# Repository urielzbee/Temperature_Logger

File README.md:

# Temperature_Logger
Temperature Data Logger

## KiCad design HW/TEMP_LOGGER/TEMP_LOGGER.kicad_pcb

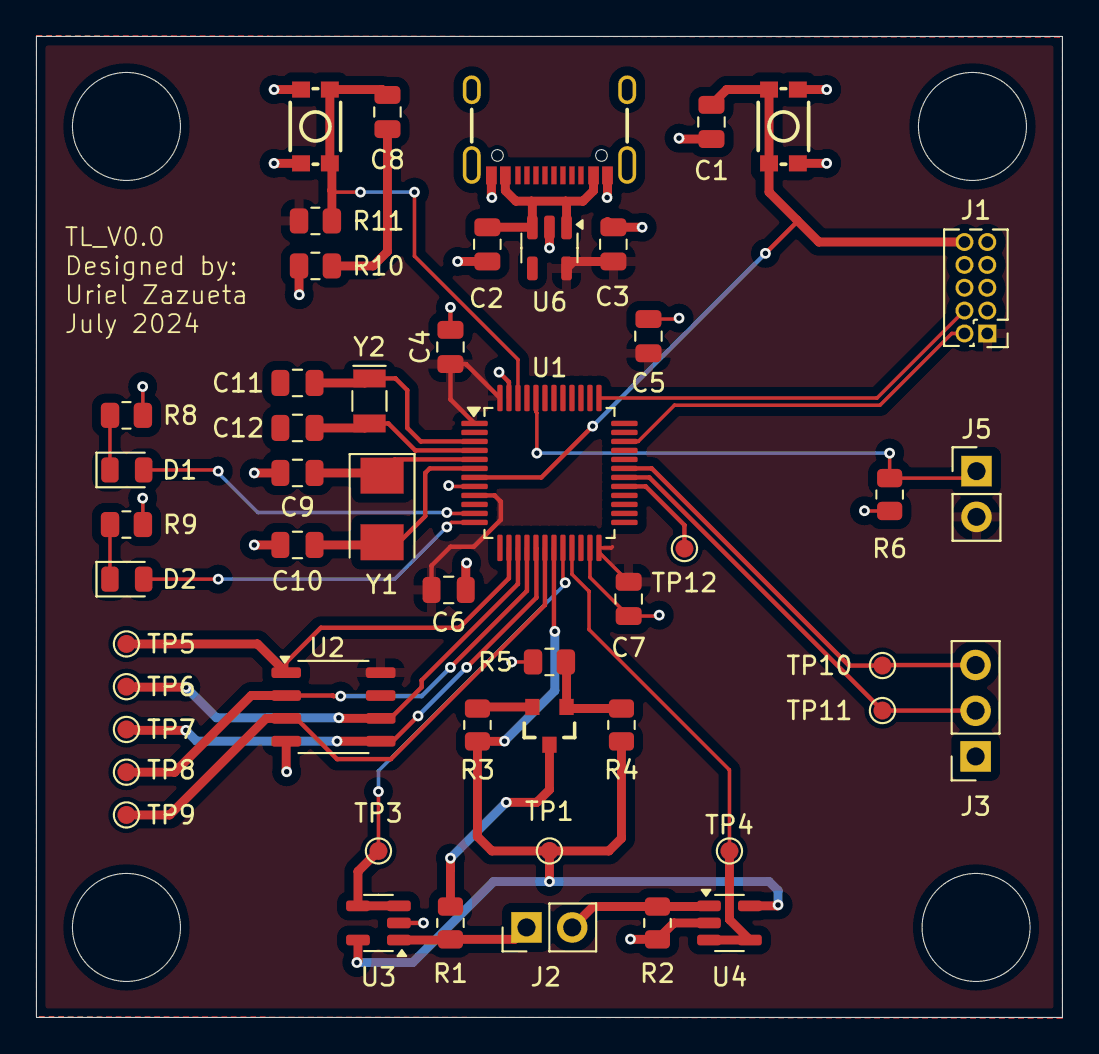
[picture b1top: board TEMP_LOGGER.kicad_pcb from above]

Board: 2 copper layers, 57.0 x 54.5 mm, 50 parts (0 on the bottom side), 33 nets.

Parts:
C1, C4, C5, C6, C7, C8: 100nF; C_0805_2012Metric
C2, C3: 1.0uF; C_0805_2012Metric
C9, C10: 20pF; C_0805_2012Metric
C11, C12: 4.3pF; C_0805_2012Metric
D1: GREEN; LED_0805_2012Metric
D2: RED; LED_0805_2012Metric
J1: 1.27, 2x5, Male, TH; PinHeader_2x05_P1.27mm_Vertical
J2, J5: Conn_01x02; PinHeader_1x02_P2.54mm_Vertical
J3: Conn_01x03; PinSocket_1x03_P2.54mm_Vertical
J6: USB4105-GF-A-060; USB-C_16
Q1: DMP6350S; SOT23-3
R1, R2: 49.9K; R_0805_2012Metric
R3: 150K; R_0805_2012Metric
R4, R5: 10M; R_0805_2012Metric
R6: 10K; R_0805_2012Metric
R8: 510; R_0805_2012Metric
R9: 330; R_0805_2012Metric
R10, R11: 100; R_0805_2012Metric
SW1, SW2: SMD_4.6x2.8mm_h1.9mm; Push_SMD_4.6x2.8mm
TP1, TP3, TP4, TP5, TP6, TP7, TP8, TP9, TP10, TP11: TestPoint; TestPoint_Pad_D1.0mm
TP12: MCO; TestPoint_Pad_D1.0mm
U1: STM32F030C8Tx; LQFP-48_7x7mm_P0.5mm
U2: GD25Q16CSJGR; SOP-8_3.9x4.9mm_P1.27mm
U3, U4: LM321; SOT-23-5
U6: MIC5504-3.3YM5; SOT-23-5
Y1: 8.0MHz H130A-8.000-18-2030-EXT-TR; Crystal_SMD_5032-2Pin_5.0x3.2mm
Y2: 32.768 KHz CC7V-T1A; Crystal_SMD_MicroCrystal_CC7V-T1A-2Pin_3.2x1.5mm

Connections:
+3V3: C3.1, C4.1, C5.1, C6.1, C7.1, J1.1, J5.2, R11.1, U1.1 (VDD), U1.9 (VDDA), U1.24 (VDD), U1.48 (VDD), U2.8 (VCC), U6.5 (VOUT)
BOOT0: J5.1, R6.2, U1.44 (BOOT0)
BTN_1: C8.1, R11.2, SW2.2, U1.46 (PB9)
FLASH_MISO: TP8.1, U1.16 (PA6), U2.2 (O1/SO)
FLASH_MOSI: TP7.1, U1.17 (PA7), U2.5 (SI/IO0)
FLASH_SCK: TP6.1, U1.15 (PA5), U2.6 (SCLK)
FLASH_nCS: TP5.1, U1.14 (PA4), U2.1 (~CS)
FLASH_nWP: TP9.1, U1.18 (PB0), U2.3 (~WP)
GND: C1.2, C2.2, C3.2, C4.2, C5.2, C6.2, C7.2, C9.2, C10.2, C11.2, C12.2, J1.3, J1.5, J1.9, J3.1, J6.GND, J6.S (SHIELD), R2.2, R5.2, R6.1, R8.1, R9.1, R10.2, SW1.1, SW2.1, U1.8 (VSSA), U1.23 (VSS), U1.47 (VSS), U2.4 (VSS), U3.2 (V-), U4.2 (V-), U6.2 (GND)
LED0: D1.2 (A), U1.11 (PA1)
LED1: D2.2 (A), U1.12 (PA2)
NRST: C1.1, J1.10, SW1.2, U1.7 (NRST)
unnamed: C8.2, R10.1
unnamed: D1.1 (K), R8.2
unnamed: D2.1 (K), R9.2
unnamed: J2.1, R1.2, U3.1 (+)
unnamed: J2.2, R2.1, U4.1 (+)
unnamed: Q1.3 (D), R1.1
unnamed: Q1.1 (G), R4.2, R5.1
unnamed: Q1.2 (S), R3.2
unnamed: TP12.1, U1.29 (PA8)
OSC32_IN: C11.1, U1.3 (PC14), Y2.1
OSC32_OUT: C12.1, U1.4 (PC15), Y2.2
OSC_IN: C9.1, U1.5 (PF0), Y1.1
OSC_OUT: C10.1, U1.6 (PF1), Y1.2
SWDCLK: J1.4, U1.37 (PA14)
SWDIO: J1.2, U1.34 (PA13)
TEMP_EN: R3.1, R4.1, TP1.1, U1.19 (PB1), U3.5 (V+), U4.5 (V+)
THERM_OFST: TP4.1, U1.21 (PB10), U4.3 (-), U4.4
THERM_OUT: TP3.1, U1.20 (PB2), U3.3 (-), U3.4
USART1_RX: J3.3, TP10.1, U1.31 (PA10)
USART1_TX: J3.2, TP11.1, U1.30 (PA9)
VCC: C2.1, J6.VBUS, U6.1 (VIN), U6.3 (EN)

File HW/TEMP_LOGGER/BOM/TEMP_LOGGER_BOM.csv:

"Reference","Value","Footprint","Qty","Mfg Part#"
"C1,C4,C5,C6,C7,C8","100nF","Capacitor_SMD:C_0805_2012Metric","6",""
"C2,C3","1.0uF","Capacitor_SMD:C_0805_2012Metric","2",""
"C9,C10","20pF","Capacitor_SMD:C_0805_2012Metric","2",""
"C11,C12","4.3pF","Capacitor_SMD:C_0805_2012Metric","2",""
"D1","GREEN","LED_SMD:LED_0805_2012Metric","1",""
"D2","RED","LED_SMD:LED_0805_2012Metric","1",""
"J1","1.27, 2x5, Male, TH","Connector_PinHeader_1.27mm:PinHeader_2x05_P1.27mm_Vertical","1",""
"J2,J5","Conn_01x02","Connector_PinHeader_2.54mm:PinHeader_1x02_P2.54mm_Vertical","2",""
"J3","Conn_01x03","Connector_PinSocket_2.54mm:PinSocket_1x03_P2.54mm_Vertical","1",""
"J6","USB4105-GF-A-060","SparkFun-Connector:USB-C_16","1",""
"Q1","DMP6350S","SparkFun-Semiconductor-Standard:SOT23-3","1",""
"R1,R2","49.9K","Resistor_SMD:R_0805_2012Metric","2",""
"R3","150K","Resistor_SMD:R_0805_2012Metric","1",""
"R4,R5","10M","Resistor_SMD:R_0805_2012Metric","2",""
"R6","10K","Resistor_SMD:R_0805_2012Metric","1",""
"R8","510","Resistor_SMD:R_0805_2012Metric","1",""
"R9","330","Resistor_SMD:R_0805_2012Metric","1",""
"R10,R11","100","Resistor_SMD:R_0805_2012Metric","2",""
"SW1,SW2","SMD_4.6x2.8mm_h1.9mm","SparkFun-Switch:Push_SMD_4.6x2.8mm","2",""
"U1","STM32F030C8Tx","Package_QFP:LQFP-48_7x7mm_P0.5mm","1",""
"U2","GD25Q16CSJGR ","Package_SO:SOP-8_3.9x4.9mm_P1.27mm","1",""
"U3,U4","LM321","Package_TO_SOT_SMD:SOT-23-5","2",""
"U6","MIC5504-3.3YM5","Package_TO_SOT_SMD:SOT-23-5","1",""
"Y1","8.0MHz H130A-8.000-18-2030-EXT-TR","Crystal:Crystal_SMD_5032-2Pin_5.0x3.2mm","1",""
"Y2","32.768 KHz CC7V-T1A","Crystal:Crystal_SMD_MicroCrystal_CC7V-T1A-2Pin_3.2x1.5mm","1",""

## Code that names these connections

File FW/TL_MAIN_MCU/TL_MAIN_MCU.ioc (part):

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Mcu.Name=STM32F030C8Tx
Mcu.Package=LQFP48
Mcu.UserName=STM32F030C8Tx
PA1.GPIOParameters=GPIO_Label
PA1.GPIO_Label=LED0
PA1.Signal=GPIO_Output
PA10.Mode=Asynchronous
PA10.Signal=USART1_RX
PA13.Mode=Serial_Wire
PA13.Signal=SYS_SWDIO
PA14.Mode=Serial_Wire
PA14.Signal=SYS_SWCLK
PA2.GPIOParameters=GPIO_Label
PA2.GPIO_Label=LED1
PA2.Signal=GPIO_Output
PA4.GPIOParameters=GPIO_Label
PA4.GPIO_Label=FLASH_nCS
PA4.Signal=GPIO_Output
PA5.GPIOParameters=GPIO_Label
PA5.GPIO_Label=FLASH_SCK
PA5.Mode=Full_Duplex_Master
PA5.Signal=SPI1_SCK
PA6.GPIOParameters=GPIO_Label
PA6.GPIO_Label=FLASH_MISO
PA6.Mode=Full_Duplex_Master
PA6.Signal=SPI1_MISO
PA7.GPIOParameters=GPIO_Label
PA7.GPIO_Label=FLASH_MOSI
PA7.Mode=Full_Duplex_Master
PA7.Signal=SPI1_MOSI
PA8.GPIOParameters=GPIO_Label
PA8.GPIO_Label=MCO
PA8.Mode=Clock-out
PA8.Signal=RCC_MCO
PA9.Mode=Asynchronous
PA9.Signal=USART1_TX
PB0.GPIOParameters=GPIO_Label
PB0.GPIO_Label=FLASH_nWP
PB0.Signal=GPIO_Output
PB1.GPIOParameters=GPIO_Label
PB1.GPIO_Label=TEMP_EN
PB1.Signal=GPIO_Output
PB10.GPIOParameters=GPIO_Label
PB10.GPIO_Label=THERM_OFST
PB10.Signal=GPIO_Analog
PB2.GPIOParameters=GPIO_Label
PB2.GPIO_Label=THERM_OFST
PB2.Signal=GPIO_Analog
PB9.GPIOParameters=GPIO_Label
PB9.GPIO_Label=BTN_1
PB9.Signal=GPIO_Input
PC14-OSC32_IN.Mode=LSE-External-Oscillator
PC14-OSC32_IN.Signal=RCC_OSC32_IN
PC15-OSC32_OUT.Mode=LSE-External-Oscillator
PC15-OSC32_OUT.Signal=RCC_OSC32_OUT
PF0-OSC_IN.Mode=HSE-External-Oscillator
PF0-OSC_IN.Signal=RCC_OSC_IN
PF1-OSC_OUT.Mode=HSE-External-Oscillator
PF1-OSC_OUT.Signal=RCC_OSC_OUT
board=custom

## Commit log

2024-05-30 Added cpputest submodule
2024-05-30 Incremental update
2024-05-30 Test example
2024-06-12 Added thermistor modules
2024-06-12 Updated Makefile
2024-06-22 Removed build directoy
2024-07-18 Board release V0.0
2024-07-18 Updated gitignore
2024-07-18 Remved backup file
2024-07-27 Temp backups added to gitignore
2024-07-27 Added Unity as a tools
2024-07-27 Test enviroment setup
2024-07-27 Added RTOS, Initial pin configuration
2024-07-27 SPI configuration
2024-07-28 Enabled ADC CPU temp
2024-07-28 Added Debugger configuration
    Debugger configuration
    C/C++ properties
    VS code settings
2024-07-28 Test setup update
2024-08-03 Disabled RTOS
    Not enough memory
2024-08-03 Initial CPU Temp Module
